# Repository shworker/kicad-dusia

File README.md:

# kicad-dusia
DUSIA (Dual USB to Serial Isolated Adapter) with halvanic isolation. Used for connect to PC very sensitive equipment with RS-232 ports

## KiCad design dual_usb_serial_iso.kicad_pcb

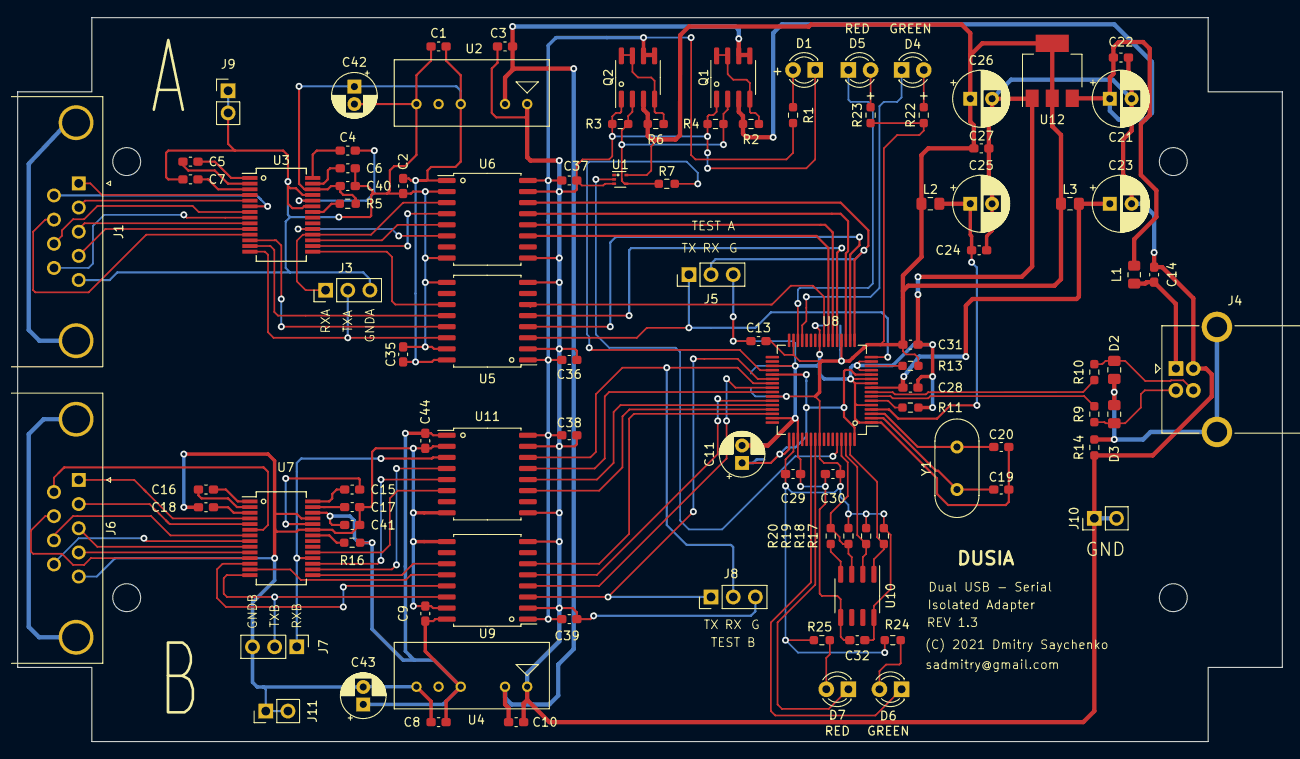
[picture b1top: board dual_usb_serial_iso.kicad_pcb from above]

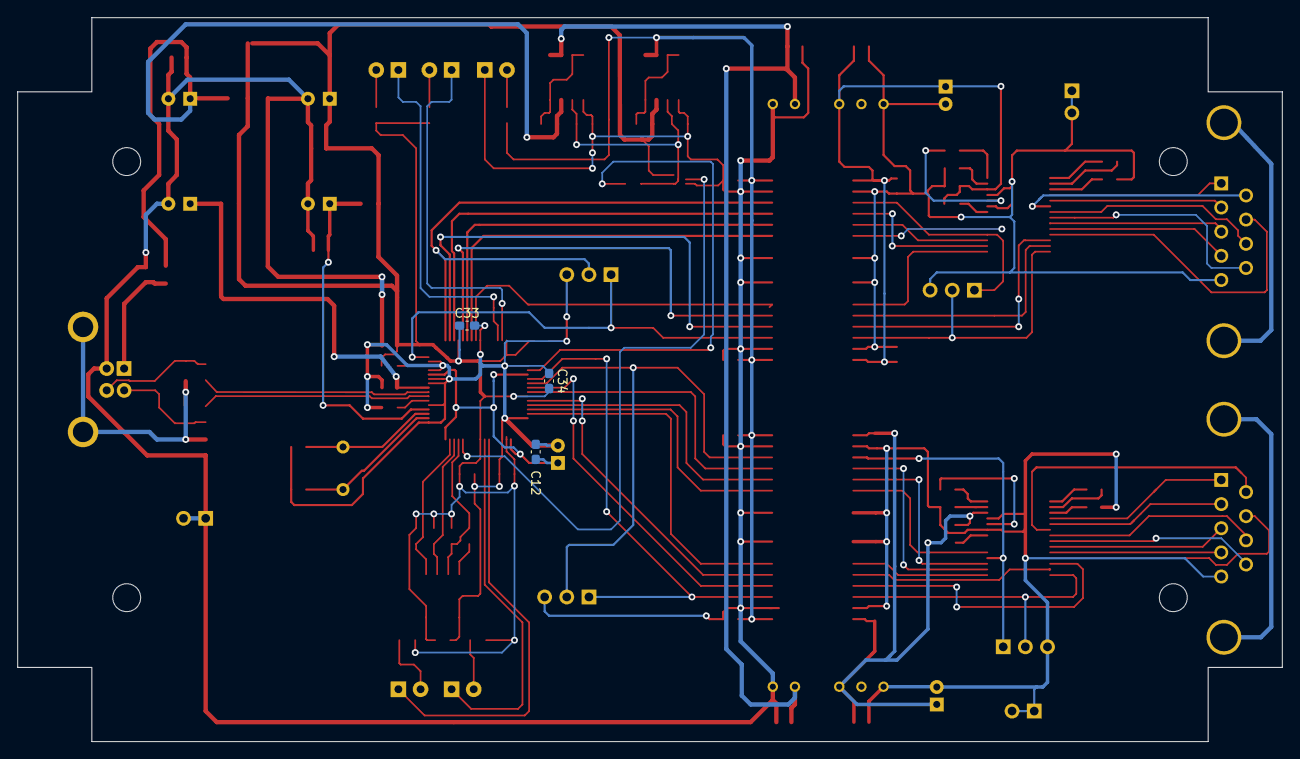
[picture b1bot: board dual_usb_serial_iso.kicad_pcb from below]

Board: 2 copper layers, 145.0 x 83.0 mm, 100 parts (3 on the bottom side), 102 nets.

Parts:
C1, C2, C3, C4, C5, C6, C7, C8, C9, C10, C12, C13, C14, C15, C16, C17, C18, C22, C24, C27, C28, C29, C30, C31, C32, C33, C34, C35, C36, C37, C38, C39, C40, C41, C44: 100n; C_0603_1608Metric_Pad1.08x0.95mm_HandSolder
C11: 4,7u; CP_Radial_D5.0mm_P2.00mm
C19, C20: 27pF; C_0603_1608Metric_Pad1.08x0.95mm_HandSolder
C21, C23, C25, C26: 4,7u; CP_Radial_D6.3mm_P2.50mm
C42, C43: 47u; CP_Radial_D5.0mm_P2.00mm
D1, D4, D6: GREEN; LED_D3.0mm
D2, D3: PGB1010603MR; C_0805_2012Metric_Pad1.18x1.45mm_HandSolder
D5, D7: RED; LED_D3.0mm
J1, J6: DB9_Male_MountingHoles; DSUB-9_Male_Horizontal_P2.77x2.84mm_EdgePinOffset4.94mm_Hou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
J3: RX_TX_Test_ISO_A; PinHeader_1x03_P2.54mm_Vertical
J4: USB_B; USB_B_OST_USB-B1HSxx_Horizontal
J5: RX_TX_test_U_A; PinHeader_1x03_P2.54mm_Vertical
J7: RX_TX_Test_ISO_B; PinHeader_1x03_P2.54mm_Vertical
J8: RX_TX_Test_U_B; PinHeader_1x03_P2.54mm_Vertical
J9: -5V_ISO_A; PinHeader_1x02_P2.54mm_Vertical
J10: GND; PinHeader_1x02_P2.54mm_Vertical
J11: -5V_ISO_B; PinHeader_1x02_P2.54mm_Vertical
L1, L2, L3: 600R; L_0805_2012Metric_Pad1.15x1.40mm_HandSolder
Q1, Q2: IRF7317; SOIC-8_3.9x4.9mm_P1.27mm
R1, R22, R23, R24, R25: 300R; R_0603_1608Metric_Pad0.98x0.95mm_HandSolder
R2, R3, R4, R5, R6, R13, R16, R17, R18, R19: 10k; R_0603_1608Metric_Pad0.98x0.95mm_HandSolder
R7, R14: 0R; R_0603_1608Metric_Pad0.98x0.95mm_HandSolder
R9, R10: 10R; R_0603_1608Metric_Pad0.98x0.95mm_HandSolder
R11: 12k; R_0603_1608Metric_Pad0.98x0.95mm_HandSolder
R20: 2k; R_0603_1608Metric_Pad0.98x0.95mm_HandSolder
U1: 74LVC1GU04DRL; SOT-553
U2, U4: TMR1-0511; SIP-6
U3, U7: MAX3241; SSOP-28_5.3x10.2mm_P0.65mm
U5, U9: ADuM1411; SOIC-16W_7.5x10.3mm_P1.27mm
U6, U11: ADuM1400xRW; SOIC-16W_7.5x10.3mm_P1.27mm
U8: FT2232HL; LQFP-64_10x10mm_P0.5mm
U10: 93LCxxB; SOIC-8_3.9x4.9mm_P1.27mm
U12: LM1117-3.3; SOT-223-3_TabPin2
Y1: 12MHz; Crystal_HC49-U_Vertical

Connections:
+3V3: C13.1, C26.1, C27.1, C29.1, C30.1, C31.1, C32.1, C33.1, C34.1, L2.1, L3.1, Q2.3, R6.2, R13.2, R17.1, R18.1, R19.1, R22.1, R23.1, R24.1, R25.1, U1.5, U8.20, U8.31, U8.42, U8.50, U8.56, U10.8, U12.2
+3V3_SW: C36.1, C37.1, C38.1, C39.1, Q2.5, Q2.6, R1.2, U5.1, U6.16, U9.1, U11.16
+5V_ISO_A: C1.1, C2.1, C35.1, C40.1, C42.1, R5.2, U2.4, U3.26, U5.16, U6.1
+5V_ISO_B: C8.1, C9.1, C41.1, C43.1, C44.1, R16.2, U4.4, U7.26, U9.16, U11.1
-5V_ISO_A: C1.2, C2.2, C6.1, C7.2, C35.2, C40.2, C42.2, J1.5, J3.3, J9.1, J9.2, U2.6, U3.23, U3.25, U5.9, U5.15, U6.2, U6.8
-5V_ISO_B: C8.2, C9.2, C17.2, C18.1, C41.2, C43.2, C44.2, J6.5, J7.3, J11.1, J11.2, U4.6, U7.23, U7.25, U9.9, U9.15, U11.2, U11.8
/#PWREN: U1.2, U8.60
/+5V_SW: C3.1, C10.1, Q1.5, Q1.6, U2.2, U4.2
/ADBUS0: J5.1, U5.3, U8.16
/ADBUS1: J5.2, U6.14, U8.17
/ADBUS2: U5.4, U8.18
/ADBUS3: U6.13, U8.19
/ADBUS4: U5.5, U8.21
/ADBUS5: U6.12, U8.22
/ADBUS6: U6.11, U8.23
/ADBUS7: U5.6, U8.24
/BDBUS0: J8.1, U8.38, U9.3
/BDBUS1: J8.2, U8.39, U11.14
/BDBUS2: U8.40, U9.4
/BDBUS3: U8.41, U11.13
/BDBUS4: U8.43, U9.5
/BDBUS5: U8.44, U11.12
/BDBUS6: U8.45, U11.11
/BDBUS7: U8.46, U9.6
/C1+A: C4.2, U3.28
/C1-A: C4.1, U3.24
/C2+A: C5.1, U3.1
/C2-A: C5.2, U3.2
/CTSA: U3.16, U6.4
/CTSB: U7.16, U11.4
/D+: D2.1, J4.3, R10.2
/D-: D3.1, J4.2, R9.2
/DCDA: U3.19, U6.6
/DCDB: U7.19, U11.6
/DSRA: U3.17, U6.5
/DSRB: U7.17, U11.5
/DTRA: U3.13, U5.12
/DTRB: U7.13, U9.12
/RD+: R10.1, U8.8
/RD-: R9.1, U8.7
/REF: R11.1, U8.6
/RESET: R13.1, U8.14
/RIA: U3.15, U5.11
/RIB: U7.15, U9.11
/RS_CTSA: J1.8, U3.7
/RS_CTSB: J6.8, U7.7
/RS_DCDA: J1.1, U3.4
/RS_DCDB: J6.1, U7.4
/RS_DSRA: J1.6, U3.6
/RS_DSRB: J6.6, U7.6
/RS_DTRA: J1.4, U3.10
/RS_DTRB: J6.4, U7.10
/RS_RIA: J1.9, U3.8
/RS_RIB: J6.9, U7.8
/RS_RTSA: J1.7, U3.11
/RS_RTSB: J6.7, U7.11
/RS_RXDA: J1.2, U3.5
/RS_RXDB: J6.2, U7.5
/RS_TXDA: J1.3, U3.9
/RS_TXDB: J6.3, U7.9
/RTSA: U3.12, U5.13
/RTSB: U7.12, U9.13
/RXDA: J3.1, U3.18, U6.3
/RXDB: J7.1, U7.18, U11.3
/SHDNA: R5.1, U3.22
/SUSPEND: R7.2, U8.36
/TXDA: J3.2, U3.14, U5.14
/TXDB: J7.2, U7.14, U9.14
/V+A: C6.2, U3.27
/V-A: C7.1, U3.3
GND: C3.2, C10.2, C11.2, C12.2, C13.2, C14.1, C19.2, C20.2, C21.2, C22.2, C23.2, C24.2, C25.2, C26.2, C27.2, C28.2, C29.2, C30.2, C31.2, C32.2, C33.2, C34.2, C36.2, C37.2, C38.2, C39.2, D1.1, J4.4, J5.3, J8.3, J10.1, J10.2, Q1.1, Q2.1, R3.2, R4.2, R11.2, R14.2, U1.3, U2.1, U4.1, U5.2, U5.8, U6.9, U6.15, U8.1, U8.5, U8.10, U8.11, U8.13, U8.15, U8.25, U8.35, U8.47, U8.51, U9.2, U9.8, U10.5, U11.9, U11.15, U12.1
unnamed: C14.2, J4.1, L1.2
unnamed: C15.1, U7.28
unnamed: C15.2, U7.24
unnamed: C16.1, U7.2
unnamed: C16.2, U7.1
unnamed: C17.1, U7.27
unnamed: C18.2, U7.3
unnamed: C19.1, U8.2, Y1.1
unnamed: C20.1, U8.3, Y1.2
unnamed: D1.2, R1.1
unnamed: D2.2, D3.2, J4.5, R14.1
unnamed: D4.2, R22.2
unnamed: D5.2, R23.2
unnamed: D6.2, R24.2
unnamed: D7.2, R25.2
unnamed: Q1.4, Q1.7, Q1.8, R2.1
unnamed: Q2.4, Q2.7, Q2.8, R6.1
unnamed: R16.1, U7.22
unnamed: R17.2, U8.63, U10.1
unnamed: R18.2, U8.62, U10.2
unnamed: R19.2, R20.1, U8.61, U10.3
unnamed: R20.2, U10.4
PWREN: Q1.2, Q2.2, R3.1, R4.1, R7.1, U1.4
RXLEDA: D4.1, U8.29
RXLEDB: D6.1, U8.54
TXLEDA: D5.1, U8.30
TXLEDB: D7.1, U8.55
VBUS: C21.1, C22.1, L1.1, Q1.3, R2.2, U12.3
VCORE: C11.1, C12.1, U8.12, U8.37, U8.49, U8.64
VPHY: C24.1, C25.1, L2.2, U8.4
VPLL: C23.1, C28.1, L3.2, U8.9

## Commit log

2021-08-12 Add files via upload
    Kicad project with schematic in PDF format and Gerber files

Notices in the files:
dual_usb_serial_iso.kicad_pcb:
(C) 2021 Dmitry Saychenko
